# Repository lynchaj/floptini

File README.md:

# floptini
Open Source USB to Floppy Drive Controller for Retrobrewcomputers &amp; hobbyists

Help Wanted: PC and STM32F4 software writers to write code for prototype USB to FDC module.  

Note: there is no software for this project right now so if you plan to help with software expect to start at the beginning.  STM32F4 experience would be beneficial

My intent is for this to be an ad-hoc team project with members having various specialities like software, firmware, hardware, disk formats, etc.

If you want to join up then you can post in the discussions on this repo or contact me on retrobrewcomputers.org

There is a thread on retrobrewcomputers.org forum discussing the topic of USB to FDC devices

https://www.retrobrewcomputers.org/forum/index.php?t=msg&th=212&start=0&

Initial hardware is designed and ready to go to PCB manufacturing.  

Assuming others join the project for writing software I will order some prototype PCBs and distribute.

If you see the hardware design needs changes or things which would make it more usable please post in discussions.

# FAQ

Why using only through-hole components?  Fair question.  I choose through-hole only for the prototype hardware phase.  Assuming development matures and software is written then hardware can be easily updated to SMD.  All the current components are available in SMD versions.  SMD could potentially could reduce PCB size dramatically but until we are sure the hardware is functioning 100% it is much easier to update PCB with through-hole components than SMD

How much do the PCBs cost?  No cost for people willing to write software.  Assuming sufficient interest to proceed with the project I will order PCBs and ship one to you for your build.  The board construction is simple enough most any hobbyist should be able to build it and the parts are commonly available.  If for some reason you cannot build your own please contact me to make arrangements for a pre-built board.

Note: the initial project was designed using an older version of KiCAD so using the project requires some conversion to newer KiCAD standards and formats.  Not a showstopper but some work required.

Note: this project sort of drifted off into the weeds.  If you are interested in adopting Floptini and doing your own build and test, please do and post your results.  There is a long standing retrocomputer community need for a general purpose USB to floppy interface (Shugart Minidisk Floppy 34-pin) rather than those cheap USB to 3.5" floppy drives that are only good for 1.44MB formatted IBM HD disks.  Floppy disks forever!

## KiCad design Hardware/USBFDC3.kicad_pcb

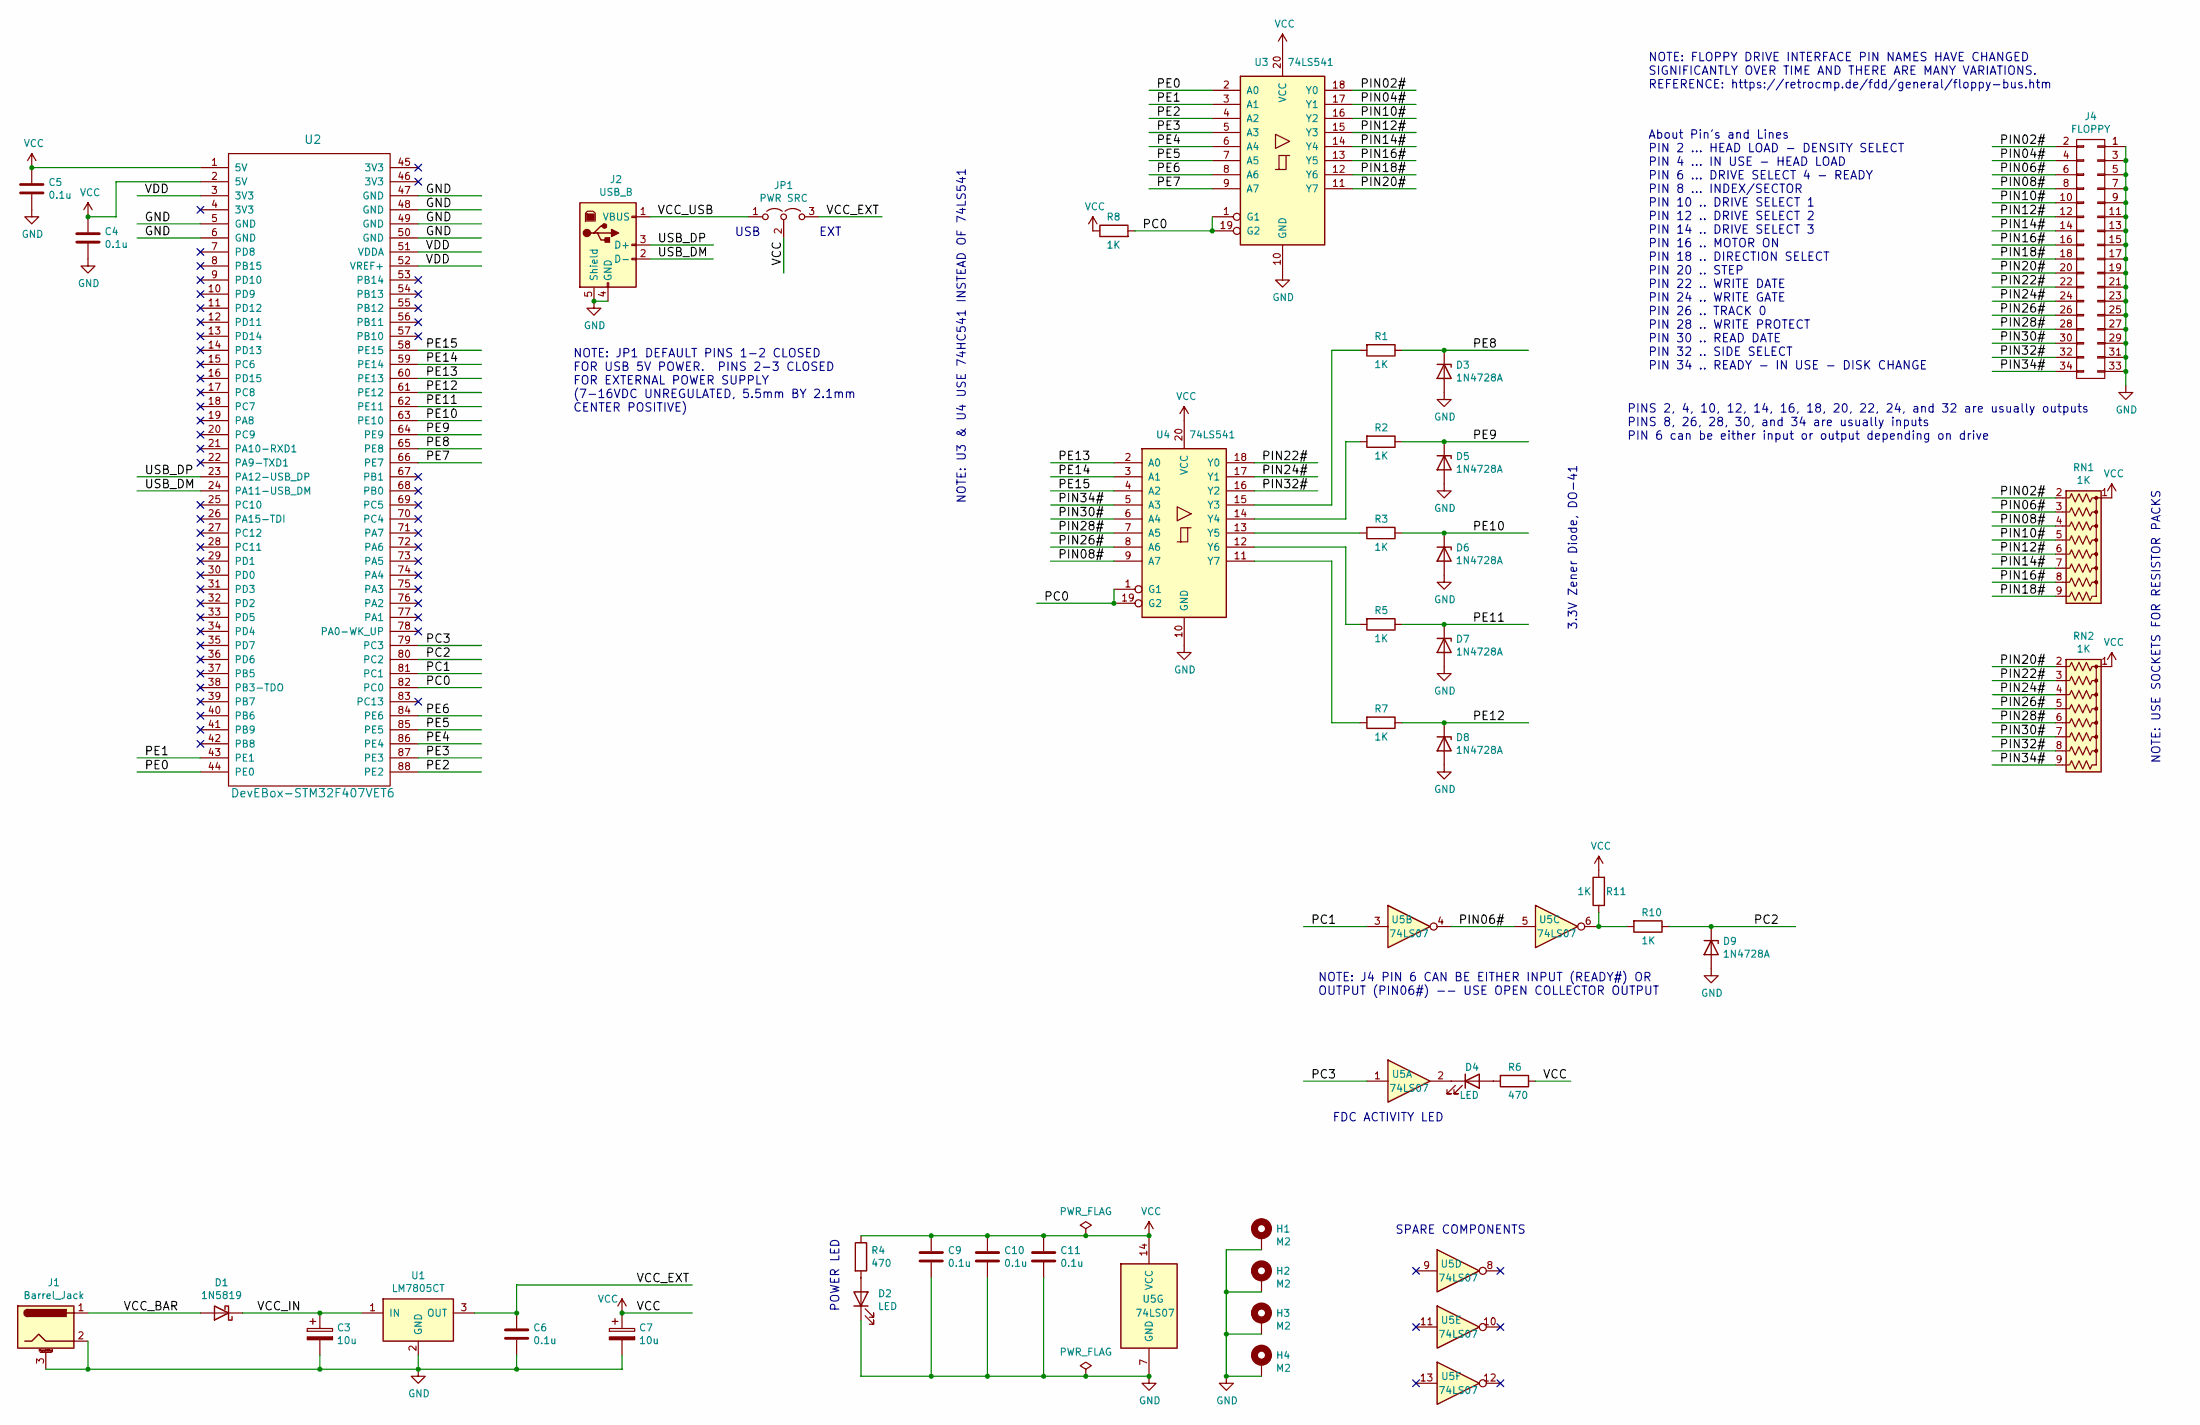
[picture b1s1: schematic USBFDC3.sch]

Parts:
C3, C7: 10u; CP_Radial_D5.0mm_P2.50mm
C4, C5, C6, C9, C10, C11: 0.1u; C_Disc_D5.0mm_W2.5mm_P5.00mm
D1: 1N5819; D_DO-41_SOD81_P10.16mm_Horizontal
D2, D4: LED; LED_D3.0mm
D3, D5, D6, D7, D8, D9: 1N4728A; D_DO-41_SOD81_P7.62mm_Horizontal
H1, H2, H3, H4: M2; MountingHole_2.2mm_M2_Pad
J1: Barrel_Jack; BarrelJack_Horizontal
J2: USB_B; USB_B_OST_USB-B1HSxx_Horizontal
J4: FLOPPY; PinHeader_2x17_P2.54mm_Horizontal
JP1: PWR SRC; PinHeader_1x03_P2.54mm_Horizontal
R1, R2, R3, R5, R7, R8, R10, R11: 1K; R_Axial_DIN0207_L6.3mm_D2.5mm_P7.62mm_Horizontal
R4, R6: 470; R_Axial_DIN0207_L6.3mm_D2.5mm_P7.62mm_Horizontal
RN1, RN2: 1K; R_Array_SIP9
U1: LM7805CT; TO-220-3_Horizontal_TabDown
U2: DevEBox-STM32F407VET6
U3, U4: 74LS541; DIP-20_W7.62mm
U5: 74LS07; DIP-14_W7.62mm

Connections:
/PC0: R8.2, U2.82 (PC0), U3.1 (G1), U3.19 (G2), U4.1 (G1), U4.19 (G2)
/PC1: U2.81 (PC1), U5.3
/PC2: D9.1 (K), R10.1, U2.80 (PC2)
/PC3: U2.79 (PC3), U5.1
/PE0: U2.44 (PE0), U3.2 (A0)
/PE1: U2.43 (PE1), U3.3 (A1)
/PE2: U2.88 (PE2), U3.4 (A2)
/PE3: U2.87 (PE3), U3.5 (A3)
/PE4: U2.86 (PE4), U3.6 (A4)
/PE5: U2.85 (PE5), U3.7 (A5)
/PE6: U2.84 (PE6), U3.8 (A6)
/PE7: U2.66 (PE7), U3.9 (A7)
/PE8: D3.1 (K), R1.1, U2.65 (PE8)
/PE9: D5.1 (K), R2.1, U2.64 (PE9)
/PE10: D6.1 (K), R3.1, U2.63 (PE10)
/PE11: D7.1 (K), R5.1, U2.62 (PE11)
/PE12: D8.1 (K), R7.1, U2.61 (PE12)
/PE13: U2.60 (PE13), U4.2 (A0)
/PE14: U2.59 (PE14), U4.3 (A1)
/PE15: U2.58 (PE15), U4.4 (A2)
/PIN02#: J4.2, RN1.2 (R1), U3.18 (Y0)
/PIN04#: J4.4, U3.17 (Y1)
/PIN06#: J4.6, RN1.3 (R2), U5.4, U5.5
/PIN08#: J4.8, RN1.4 (R3), U4.9 (A7)
/PIN10#: J4.10, RN1.5 (R4), U3.16 (Y2)
/PIN12#: J4.12, RN1.6 (R5), U3.15 (Y3)
/PIN14#: J4.14, RN1.7 (R6), U3.14 (Y4)
/PIN16#: J4.16, RN1.8 (R7), U3.13 (Y5)
/PIN18#: J4.18, RN1.9 (R8), U3.12 (Y6)
/PIN20#: J4.20, RN2.2 (R1), U3.11 (Y7)
/PIN22#: J4.22, RN2.3 (R2), U4.18 (Y0)
/PIN24#: J4.24, RN2.4 (R3), U4.17 (Y1)
/PIN26#: J4.26, RN2.5 (R4), U4.8 (A6)
/PIN28#: J4.28, RN2.6 (R5), U4.7 (A5)
/PIN30#: J4.30, RN2.7 (R6), U4.6 (A4)
/PIN32#: J4.32, RN2.8 (R7), U4.16 (Y2)
/PIN34#: J4.34, RN2.9 (R8), U4.5 (A3)
/USB_DM: J2.2 (D-), U2.24 (PA11-USB_DM)
/USB_DP: J2.3 (D+), U2.23 (PA12-USB_DP)
/VCC_BAR: D1.2 (A), J1.1
/VCC_EXT: C6.1, JP1.3 (B), U1.3 (OUT)
/VCC_IN: C3.1, D1.1 (K), U1.1 (IN)
/VCC_USB: J2.1 (VBUS), JP1.1 (A)
/VDD: U2.3 (3V3), U2.51 (VDDA), U2.52 (VREF+)
GND: C3.2, C4.2, C5.2, C6.2, C7.2, C9.2, C10.2, C11.2, D2.1 (K), D3.2 (A), D5.2 (A), D6.2 (A), D7.2 (A), D8.2 (A), D9.2 (A), H1.1, H2.1, H3.1, H4.1, J1.2, J1.3 (MountPin), J2.4 (GND), J2.5 (Shield), J4.1, J4.3, J4.5, J4.7, J4.9, J4.11, J4.13, J4.15, J4.17, J4.19, J4.21, J4.23, J4.25, J4.27, J4.29, J4.31, J4.33, U1.2 (GND), U2.5 (GND), U2.6 (GND), U2.47 (GND), U2.48 (GND), U2.49 (GND), U2.50 (GND), U3.10 (GND), U4.10 (GND), U5.7 (GND)
unnamed: D2.2 (A), R4.2
unnamed: D4.1 (K), U5.2
unnamed: D4.2 (A), R6.2
unnamed: R1.2, U4.15 (Y3)
unnamed: R2.2, U4.14 (Y4)
unnamed: R3.2, U4.13 (Y5)
unnamed: R5.2, U4.12 (Y6)
unnamed: R7.2, U4.11 (Y7)
unnamed: R10.2, R11.1, U5.6
VCC: C4.1, C5.1, C7.1, C9.1, C10.1, C11.1, JP1.2 (C), R4.1, R6.1, R8.1, R11.2, RN1.1 (common), RN2.1 (common), U2.1 (5V), U2.2 (5V), U3.20 (VCC), U4.20 (VCC), U5.14 (VCC)

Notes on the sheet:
NOTE: JP1 DEFAULT PINS 1-2 CLOSED FOR USB 5V POWER. PINS 2-3 CLOSED FOR EXTERNAL POWER SUPPLY (7-16VDC UNREGULATED, 5.5mm BY 2.1mm CENTER POSITIVE)
USB
EXT
FDC ACTIVITY LED
POWER LED
3.3V Zener Diode, DO-41
NOTE: U3 & U4 USE 74HC541 INSTEAD OF 74LS541
SPARE COMPONENTS
NOTE: USE SOCKETS FOR RESISTOR PACKS
NOTE: J4 PIN 6 CAN BE EITHER INPUT (READY#) OR OUTPUT (PIN06#) -- USE OPEN COLLECTOR OUTPUT
NOTE: FLOPPY DRIVE INTERFACE PIN NAMES HAVE CHANGED SIGNIFICANTLY OVER TIME AND THERE ARE MANY VARIATIONS. REFERENCE: https://retrocmp.de/fdd/general/floppy-bus.htm
About Pin's and Lines PIN 2 ... HEAD LOAD - DENSITY SELECT PIN 4 ... IN USE - HEAD LOAD PIN 6 ... DRIVE SELECT 4 - READY PIN 8 ... INDEX/SECTOR PIN 10 .. DRIVE SELECT 1 PIN 12 .. DRIVE SELECT 2 PIN 14 .. DRIVE SELECT 3 PIN 16 .. MOTOR ON PIN 18 .. DIRECTION SELECT PIN 20 .. STEP PIN 22 .. WRITE DAT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
PINS 2, 4, 10, 12, 14, 16, 18, 20, 22, 24, and 32 are usually outputs PINS 8, 26, 28, 30, and 34 are usually inputs PIN 6 can be either input or output depending on drive

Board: 2 copper layers, 42 parts (2 on the bottom side), 55 nets, no tracks yet.
